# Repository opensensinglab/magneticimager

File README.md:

Magnetic Imaging Tile
======

Work-in-progress.  Please use at your own risk. <br>

This is a board intended to function as a "magnetic field camera", and visualize magnetic fields. 

### Version 3.0

The major advancement of v3.0 is a dramatic increase in the speed with which the tile data can be read out.  I have achieved ~2000 frames per second (fps), which allows visualizing even quickly varying fields (e.g. those in a 60Hz transformer, or a moving motor), but it's likely that the tile can achieve even higher framerates.  Version 3.0 reduces the size of the tile to an 8x8 grid of hall effect sensors (64 total), arrayed in a 4mm grid.  The boards should also still be tile-able, with up to 4 of the boards tileable with minimal borders to create a 16x16 array. 

For more information (and a video of the v3.0 tile in use), please see: 
https://hackaday.io/project/18518-iteration-8/log/91551-a-third-high-speed-magnetic-imager-tile-draft

### Version 2.0

Version 2.0 consists of an array of 12x12 hall effect sensors (144 total) that sense magnetic fields, arrayed in a 4mm grid.  Each sensor is connected to an array of analog switches, that allow an individual sensor to be addressed.  Read out is accomplished one magnetic "pixel" at a time, selecting a given hall sensor from the array, reading it's value (either using the internal ADC, or an external ADC), and repeating this process until the entire array has been read out.  

The current array is designed to be tile-able, with up to four of the boards (24x24 magnetic field sensors) arrayed together. 

The Arduino firmware has a framerate of approximately 10 frames per second, when the image data is streamed over the serial port and displayed using the Processing visualization.  The Raspberry Pi Python example achieves approximately 30fps.  The array itself is likely capable of much higher speeds, but one of the major limiting factors is currently the speed of the I2C I/O multiplexer (used to select which magnetometer to read from). 

For more information (and a video of the v2.0 tile in use), please see: 
https://hackaday.io/project/18518-iteration-8/log/64376-a-magnetic-imager-tile

# Open Source

This project is open source software and hardware, and is released under various open licenses.

# Disclaimer

**DISCLAIMER OF WARRANTIES AND LIMITATION OF LIABILITY.**

UNLESS OTHERWISE SEPARATELY UNDERTAKEN BY THE LICENSOR, TO THE EXTENT POSSIBLE, THE LICENSOR OFFERS THE LICENSED MATERIAL AS-IS AND AS-AVAILABLE, AND MAKES NO REPRESENTATIONS OR WARRANTIES OF ANY KIND CONCERNING THE LICENSED MATERIAL, WHETHER EXPRESS, IMPLIED, STATUTORY, OR OTHER. THIS INCLUDES, WITHOUT LIMITATION, WARRANTIES OF TITLE, MERCHANTABILITY, FITNESS FOR A PARTICULAR PURPOSE, NON-INFRINGEMENT, ABSENCE OF LATENT OR OTHER DEFECTS, ACCURACY, OR THE PRESENCE OR ABSENCE OF ERRORS, WHETHER OR NOT KNOWN OR DISCOVERABLE. WHERE DISCLAIMERS OF WARRANTIES ARE NOT ALLOWED IN FULL OR IN PART, THIS DISCLAIMER MAY NOT APPLY TO YOU.

TO THE EXTENT POSSIBLE, IN NO EVENT WILL THE LICENSOR BE LIABLE TO YOU ON ANY LEGAL THEORY (INCLUDING, WITHOUT LIMITATION, NEGLIGENCE) OR OTHERWISE FOR ANY DIRECT, SPECIAL, INDIRECT, INCIDENTAL, CONSEQUENTIAL, PUNITIVE, EXEMPLARY, OR OTHER LOSSES, COSTS, EXPENSES, OR DAMAGES ARISING OUT OF THIS PUBLIC LICENSE OR USE OF THE LICENSED MATERIAL, EVEN IF THE LICENSOR HAS BEEN ADVISED OF THE POSSIBILITY OF SUCH LOSSES, COSTS, EXPENSES, OR DAMAGES. WHERE A LIMITATION OF LIABILITY IS NOT ALLOWED IN FULL OR IN PART, THIS LIMITATION MAY NOT APPLY TO YOU.

THE DISCLAIMER OF WARRANTIES AND LIMITATION OF LIABILITY PROVIDED ABOVE SHALL BE INTERPRETED IN A MANNER THAT, TO THE EXTENT POSSIBLE, MOST CLOSELY APPROXIMATES AN ABSOLUTE DISCLAIMER AND WAIVER OF ALL LIABILITY.

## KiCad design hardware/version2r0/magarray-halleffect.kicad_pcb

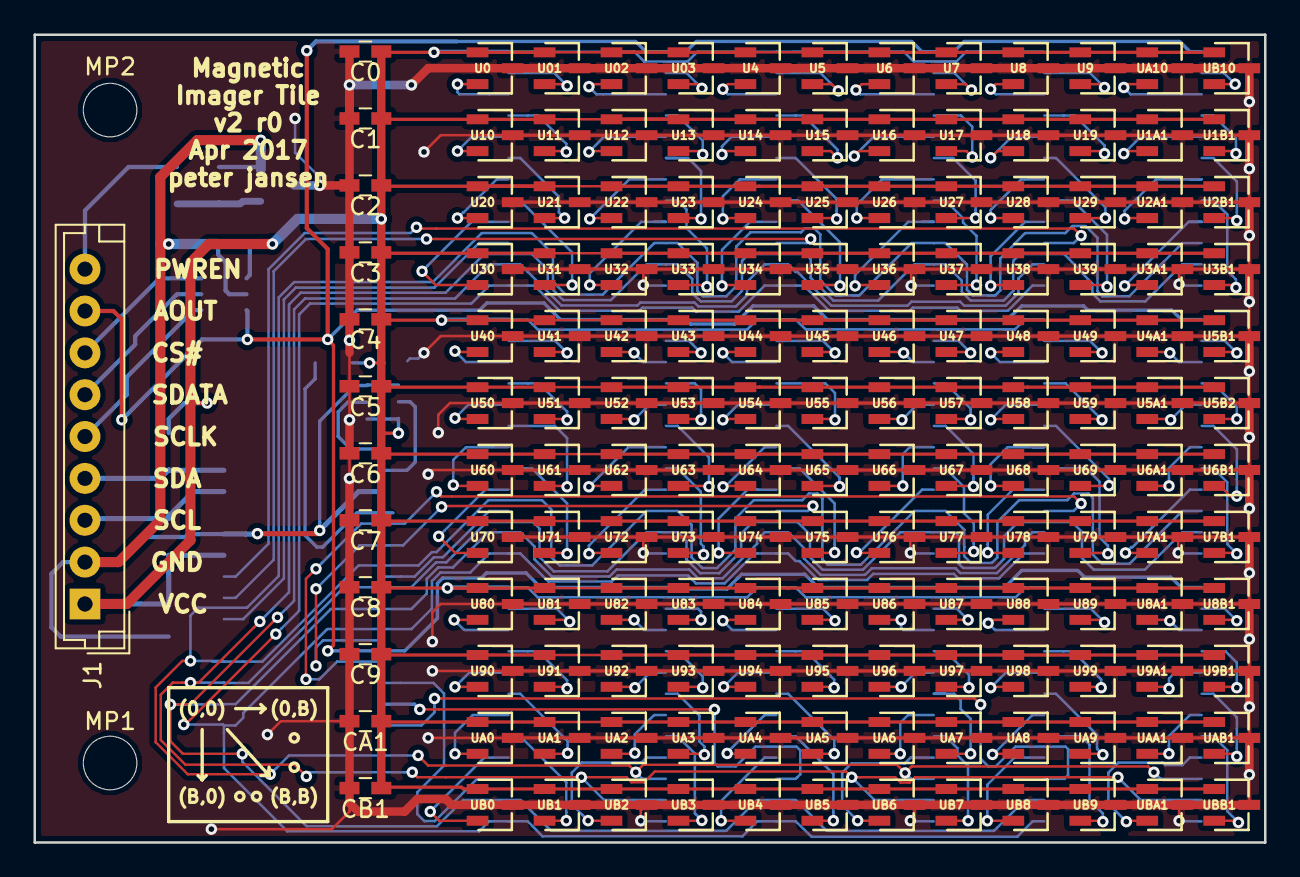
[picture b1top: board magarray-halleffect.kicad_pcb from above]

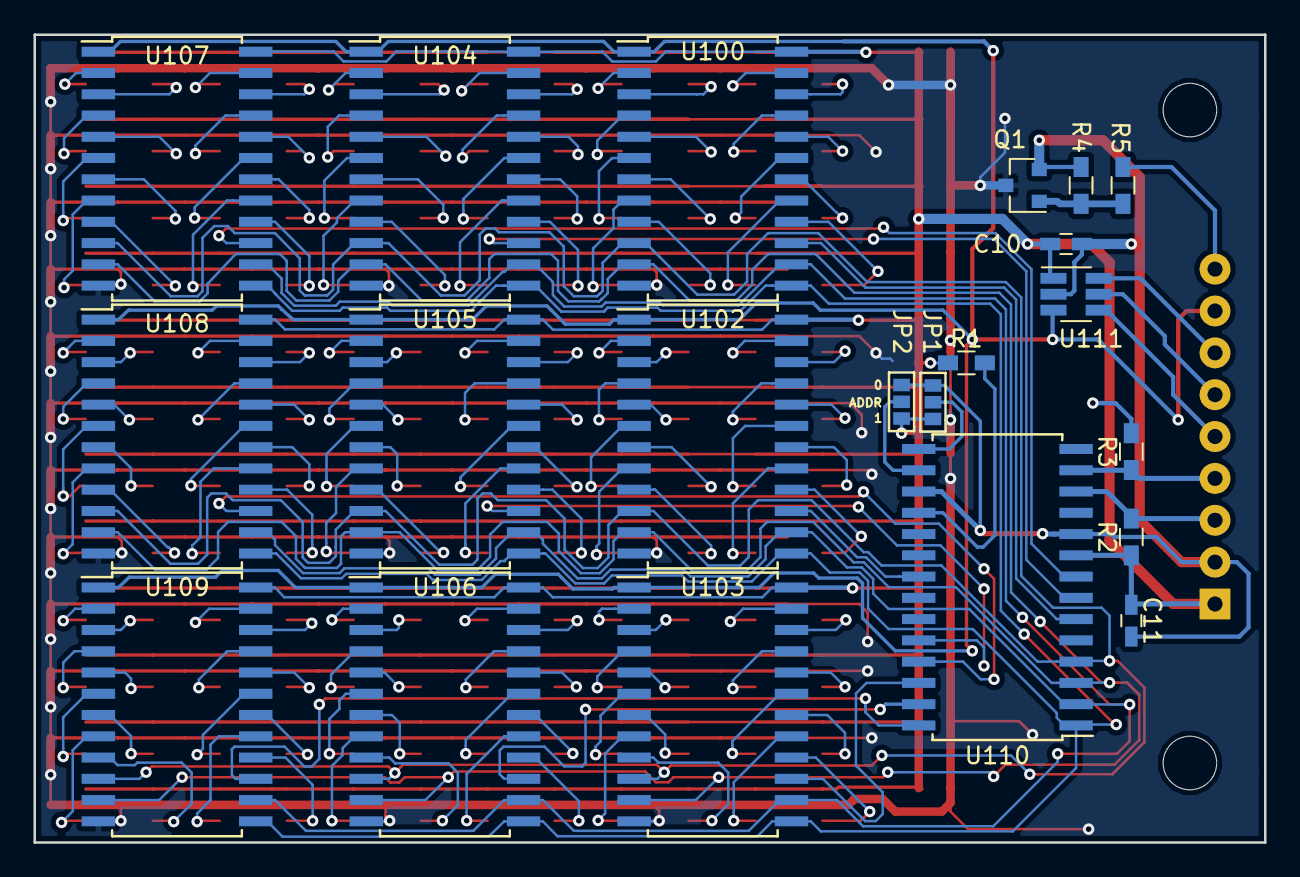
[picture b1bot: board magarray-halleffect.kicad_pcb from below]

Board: 2 copper layers, 73.5 x 48.2 mm, 180 parts (21 on the bottom side), 171 nets.

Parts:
C0, C1, C2, C3, C4, C5, C6, C7, C8, C9: 1uF; C_0603_HandSoldering
C10, C11: 4.7uF; C_0603_HandSoldering
CA1: 1uF; C_0603_HandSoldering
CB1: 1uF; C_0603_HandSoldering
J1: CONN_01X09; JST_EH_B09B-EH-A_09x2.50mm_Straight
JP1, JP2: Jumper_NC_Dual; SOLDERJUMPER-2WAY
MP1, MP2: MountingHole_3.2mm_M3
Q1: MMBF170; SOT-23
R1, R4: 10k; R_0603_HandSoldering
R2, R3: 4.7k; R_0603_HandSoldering
R5: 10; R_0603_HandSoldering
U0, U01, U1A1, U1B1, U02, U2A1, U2B1, U03, U3A1, U3B1, U4, U4A1, U5, U5A1, U5B1, U5B2, U6, U6A1, U6B1, U7, U7A1, U7B1, U8, U8A1, U8B1, U9, U9A1, U9B1, U10, U11, U12, U13, U14, U15, U16, U17, U18, U19, U20, U21, U22, U23, U24, U25, U26, U27, U28, U29, U30, U31, U32, U33, U34, U35, U36, U37, U38, U39, U40, U41, U42, U43, U44, U45, U46, U47, U48, U49, U50, U51, U52, U53, U54, U55, U56, U57, U58, U59, U60, U61, U62, U63, U64, U65, U66, U67, U68, U69, U70, U71, U72, U73, U74, U75, U76, U77, U78, U79, U80, U81, U82, U83, U84, U85, U86, U87, U88, U89, U90, U91, U92, U93, U94, U95, U96, U97, U98, U99: DRV5053; SOT-23
U100, U102, U103, U104, U105, U106, U107, U108, U109: CD74HC4067M; SOIC-24W_7.5x15.4mm_Pitch1.27mm
U110: MCP23017; SOIC-28W_7.5x17.9mm_Pitch1.27mm
U111: AD7940; SOT-23-6_Handsoldering
UA0, UA1, UA2, UA3, UA4, UA5, UA6, UA7, UA8, UA9, UA10: DRV5053; SOT-23
UAA1: DRV5053; SOT-23
UAB1: DRV5053; SOT-23
UB0, UB1, UB2, UB3, UB4, UB5, UB6, UB7, UB8, UB9, UB10: DRV5053; SOT-23
UBA1: DRV5053; SOT-23
UBB1: DRV5053; SOT-23

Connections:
/2I0: U72.2, U102.9
/2I1: U73.2, U102.8
/2I2: U62.2, U102.7
/2I3: U63.2, U102.6
/2I4: U52.2, U102.5
/2I5: U53.2, U102.4
/2I6: U42.2, U102.3
/2I7: U43.2, U102.2
/2I8: U41.2, U102.23
/2I9: U40.2, U102.22
/2I10: U51.2, U102.21
/2I11: U50.2, U102.20
/2I12: U61.2, U102.19
/2I13: U60.2, U102.18
/2I14: U71.2, U102.17
/2I15: U70.2, U102.16
/3I0: U103.9, UB2.2
/3I1: U103.8, UB3.2
/3I2: U103.7, UA2.2
/3I3: U103.6, UA3.2
/3I4: U92.2, U103.5
/3I5: U93.2, U103.4
/3I6: U82.2, U103.3
/3I7: U83.2, U103.2
/3I8: U81.2, U103.23
/3I9: U80.2, U103.22
/3I10: U91.2, U103.21
/3I11: U90.2, U103.20
/3I12: U103.19, UA1.2
/3I13: U103.18, UA0.2
/3I14: U103.17, UB1.2
/3I15: U103.16, UB0.2
/4I0: U36.2, U104.9
/4I1: U37.2, U104.8
/4I2: U26.2, U104.7
/4I3: U27.2, U104.6
/4I4: U16.2, U104.5
/4I5: U17.2, U104.4
/4I6: U6.2, U104.3
/4I7: U7.2, U104.2
/4I8: U5.2, U104.23
/4I9: U4.2, U104.22
/4I10: U15.2, U104.21
/4I11: U14.2, U104.20
/4I12: U25.2, U104.19
/4I13: U24.2, U104.18
/4I14: U35.2, U104.17
/4I15: U34.2, U104.16
/5I0: U76.2, U105.9
/5I1: U77.2, U105.8
/5I2: U66.2, U105.7
/5I3: U67.2, U105.6
/5I4: U56.2, U105.5
/5I5: U57.2, U105.4
/5I6: U46.2, U105.3
/5I7: U47.2, U105.2
/5I8: U45.2, U105.23
/5I9: U44.2, U105.22
/5I10: U55.2, U105.21
/5I11: U54.2, U105.20
/5I12: U65.2, U105.19
/5I13: U64.2, U105.18
/5I14: U75.2, U105.17
/5I15: U74.2, U105.16
/6I0: U106.9, UB6.2
/6I1: U106.8, UB7.2
/6I2: U106.7, UA6.2
/6I3: U106.6, UA7.2
/6I4: U96.2, U106.5
/6I5: U97.2, U106.4
/6I6: U86.2, U106.3
/6I7: U87.2, U106.2
/6I8: U85.2, U106.23
/6I9: U84.2, U106.22
/6I10: U95.2, U106.21
/6I11: U94.2, U106.20
/6I12: U106.19, UA5.2
/6I13: U106.18, UA4.2
/6I14: U106.17, UB5.2
/6I15: U106.16, UB4.2
/7I0: U3A1.2, U107.9
/7I1: U3B1.2, U107.8
/7I2: U2A1.2, U107.7
/7I3: U2B1.2, U107.6
/7I4: U1A1.2, U107.5
/7I5: U1B1.2, U107.4
/7I6: U107.3, UA10.2
/7I7: U107.2, UB10.2
/7I8: U9.2, U107.23
/7I9: U8.2, U107.22
/7I10: U19.2, U107.21
/7I11: U18.2, U107.20
/7I12: U29.2, U107.19
/7I13: U28.2, U107.18
/7I14: U39.2, U107.17
/7I15: U38.2, U107.16
/8I0: U7A1.2, U108.9
/8I1: U7B1.2, U108.8
/8I2: U6A1.2, U108.7
/8I3: U6B1.2, U108.6
/8I4: U5A1.2, U108.5
/8I5: U5B2.2, U108.4
/8I6: U4A1.2, U108.3
/8I7: U5B1.2, U108.2
/8I8: U49.2, U108.23
/8I9: U48.2, U108.22
/8I10: U59.2, U108.21
/8I11: U58.2, U108.20
/8I12: U69.2, U108.19
/8I13: U68.2, U108.18
/8I14: U79.2, U108.17
/8I15: U78.2, U108.16
/9I0: U109.9, UBA1.2
/9I1: U109.8, UBB1.2
/9I2: U109.7, UAA1.2
/9I3: U109.6, UAB1.2
/9I4: U9A1.2, U109.5
/9I5: U9B1.2, U109.4
/9I6: U8A1.2, U109.3
/9I7: U8B1.2, U109.2
/9I8: U89.2, U109.23
/9I9: U88.2, U109.22
/9I10: U99.2, U109.21
/9I11: U98.2, U109.20
/9I12: U109.19, UA9.2
/9I13: U109.18, UA8.2
/9I14: U109.17, UB9.2
/9I15: U109.16, UB8.2
/CS#: J1.7, U111.6
/EN1: U100.15, U110.6
/EN2: U102.15, U110.21
/EN3: U103.15, U110.26
/EN4: U104.15, U110.7
/EN5: U105.15, U110.24
/EN6: U106.15, U110.27
/EN7: U107.15, U110.8
/EN8: U108.15, U110.25
/EN9: U109.15, U110.28
/I0: U32.2, U100.9
/I1: U33.2, U100.8
/I2: U22.2, U100.7
/I3: U23.2, U100.6
/I4: U12.2, U100.5
/I5: U13.2, U100.4
/I6: U02.2, U100.3
/I7: U03.2, U100.2
/I8: U01.2, U100.23
/I9: U0.2, U100.22
/I10: U11.2, U100.21
/I11: U10.2, U100.20
/I12: U21.2, U100.19
/I13: U20.2, U100.18
/I14: U31.2, U100.17
/I15: U30.2, U100.16
/OUT: J1.8, U100.1, U102.1, U103.1, U104.1, U105.1, U106.1, U107.1, U108.1, U109.1, U111.3
/PWREN: J1.9, R5.2
/S0: U100.10, U102.10, U103.10, U104.10, U105.10, U106.10, U107.10, U108.10, U109.10, U110.4
/S1: U100.11, U102.11, U103.11, U104.11, U105.11, U106.11, U107.11, U108.11, U109.11, U110.3
/S2: U100.14, U102.14, U103.14, U104.14, U105.14, U106.14, U107.14, U108.14, U109.14, U110.2
/S3: U100.13, U102.13, U103.13, U104.13, U105.13, U106.13, U107.13, U108.13, U109.13, U110.1
/SCL: J1.3, R2.2, U110.12
/SCLK: J1.5, U111.4
/SDA: J1.4, R3.1, U110.13
/SDATA: J1.6, U111.5
GND: C0.2, C1.2, C2.2, C3.2, C4.2, C5.2, C6.2, C7.2, C8.2, C9.2, CA1.2, CB1.2, Q1.3, U0.3, U01.3, U1A1.3, U1B1.3, U02.3, U2A1.3, U2B1.3, U03.3, U3A1.3, U3B1.3, U4.3, U4A1.3, U5.3, U5A1.3, U5B1.3, U5B2.3, U6.3, U6A1.3, U6B1.3, U7.3, U7A1.3, U7B1.3, U8.3, U8A1.3, U8B1.3, U9.3, U9A1.3, U9B1.3, U10.3, U11.3, U12.3, U13.3, U14.3, U15.3, U16.3, U17.3, U18.3, U19.3, U20.3, U21.3, U22.3, U23.3, U24.3, U25.3, U26.3, U27.3, U28.3, U29.3, U30.3, U31.3, U32.3, U33.3, U34.3, U35.3, U36.3, U37.3, U38.3, U39.3, U40.3, U41.3, U42.3, U43.3, U44.3, U45.3, U46.3, U47.3, U48.3, U49.3, U50.3, U51.3, U52.3, U53.3, U54.3, U55.3, U56.3, U57.3, U58.3, U59.3, U60.3, U61.3, U62.3, U63.3, U64.3, U65.3, U66.3, U67.3, U68.3, U69.3, U70.3, U71.3, U72.3, U73.3, U74.3, U75.3, U76.3, U77.3, U78.3, U79.3, U80.3, U81.3, U82.3, U83.3, U84.3, U85.3, U86.3, U87.3, U88.3, U89.3, U90.3, U91.3, U92.3, U93.3, U94.3, U95.3, U96.3, U97.3, U98.3, U99.3, U100.12, U102.12, U103.12, U104.12, U105.12, U106.12, U107.12, U108.12, U109.12, UA0.3, UA1.3, UA2.3, UA3.3, UA4.3, UA5.3, UA6.3, UA7.3, UA8.3, UA9.3, UA10.3, UAA1.3, UAB1.3, UB0.3, UB1.3, UB2.3, UB3.3, UB4.3, UB5.3, UB6.3, UB7.3, UB8.3, UB9.3, UB10.3, UBA1.3, UBB1.3
GNDPWR: C10.2, C11.2, J1.2, JP1.1, JP2.1, Q1.2, R4.2, U110.10, U110.17, U111.2
unnamed: JP1.2, U110.15
unnamed: JP2.2, U110.16
unnamed: Q1.1, R4.1, R5.1
unnamed: R1.2, U110.18
VCC: C0.1, C1.1, C2.1, C3.1, C4.1, C5.1, C6.1, C7.1, C8.1, C9.1, C10.1, C11.1, CA1.1, CB1.1, J1.1, JP1.3, JP2.3, R1.1, R2.1, R3.2, U0.1, U01.1, U1A1.1, U1B1.1, U02.1, U2A1.1, U2B1.1, U03.1, U3A1.1, U3B1.1, U4.1, U4A1.1, U5.1, U5A1.1, U5B1.1, U5B2.1, U6.1, U6A1.1, U6B1.1, U7.1, U7A1.1, U7B1.1, U8.1, U8A1.1, U8B1.1, U9.1, U9A1.1, U9B1.1, U10.1, U11.1, U12.1, U13.1, U14.1, U15.1, U16.1, U17.1, U18.1, U19.1, U20.1, U21.1, U22.1, U23.1, U24.1, U25.1, U26.1, U27.1, U28.1, U29.1, U30.1, U31.1, U32.1, U33.1, U34.1, U35.1, U36.1, U37.1, U38.1, U39.1, U40.1, U41.1, U42.1, U43.1, U44.1, U45.1, U46.1, U47.1, U48.1, U49.1, U50.1, U51.1, U52.1, U53.1, U54.1, U55.1, U56.1, U57.1, U58.1, U59.1, U60.1, U61.1, U62.1, U63.1, U64.1, U65.1, U66.1, U67.1, U68.1, U69.1, U70.1, U71.1, U72.1, U73.1, U74.1, U75.1, U76.1, U77.1, U78.1, U79.1, U80.1, U81.1, U82.1, U83.1, U84.1, U85.1, U86.1, U87.1, U88.1, U89.1, U90.1, U91.1, U92.1, U93.1, U94.1, U95.1, U96.1, U97.1, U98.1, U99.1, U100.24, U102.24, U103.24, U104.24, U105.24, U106.24, U107.24, U108.24, U109.24, U110.9, U111.1, UA0.1, UA1.1, UA2.1, UA3.1, UA4.1, UA5.1, UA6.1, UA7.1, UA8.1, UA9.1, UA10.1, UAA1.1, UAB1.1, UB0.1, UB1.1, UB2.1, UB3.1, UB4.1, UB5.1, UB6.1, UB7.1, UB8.1, UB9.1, UB10.1, UBA1.1, UBB1.1

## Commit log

2017-07-29 Added readme, license
2017-07-29 added v2r0 hardware
2017-07-29 Added python example for raspberry pi
2017-07-29 Added Arduino and Processing code
2017-07-29 added errata for v2r0
2017-07-29 minor changes
2017-12-31 Added v3r0 imager tile, a smaller 8x8 version of v2, with a binary counter incrementing interface
2018-02-12 added schematic
2018-02-12 Added v3 code
2018-02-12 readme update
2019-09-13 Added Python/Raspberry Pi example for magnetic tile version 3
